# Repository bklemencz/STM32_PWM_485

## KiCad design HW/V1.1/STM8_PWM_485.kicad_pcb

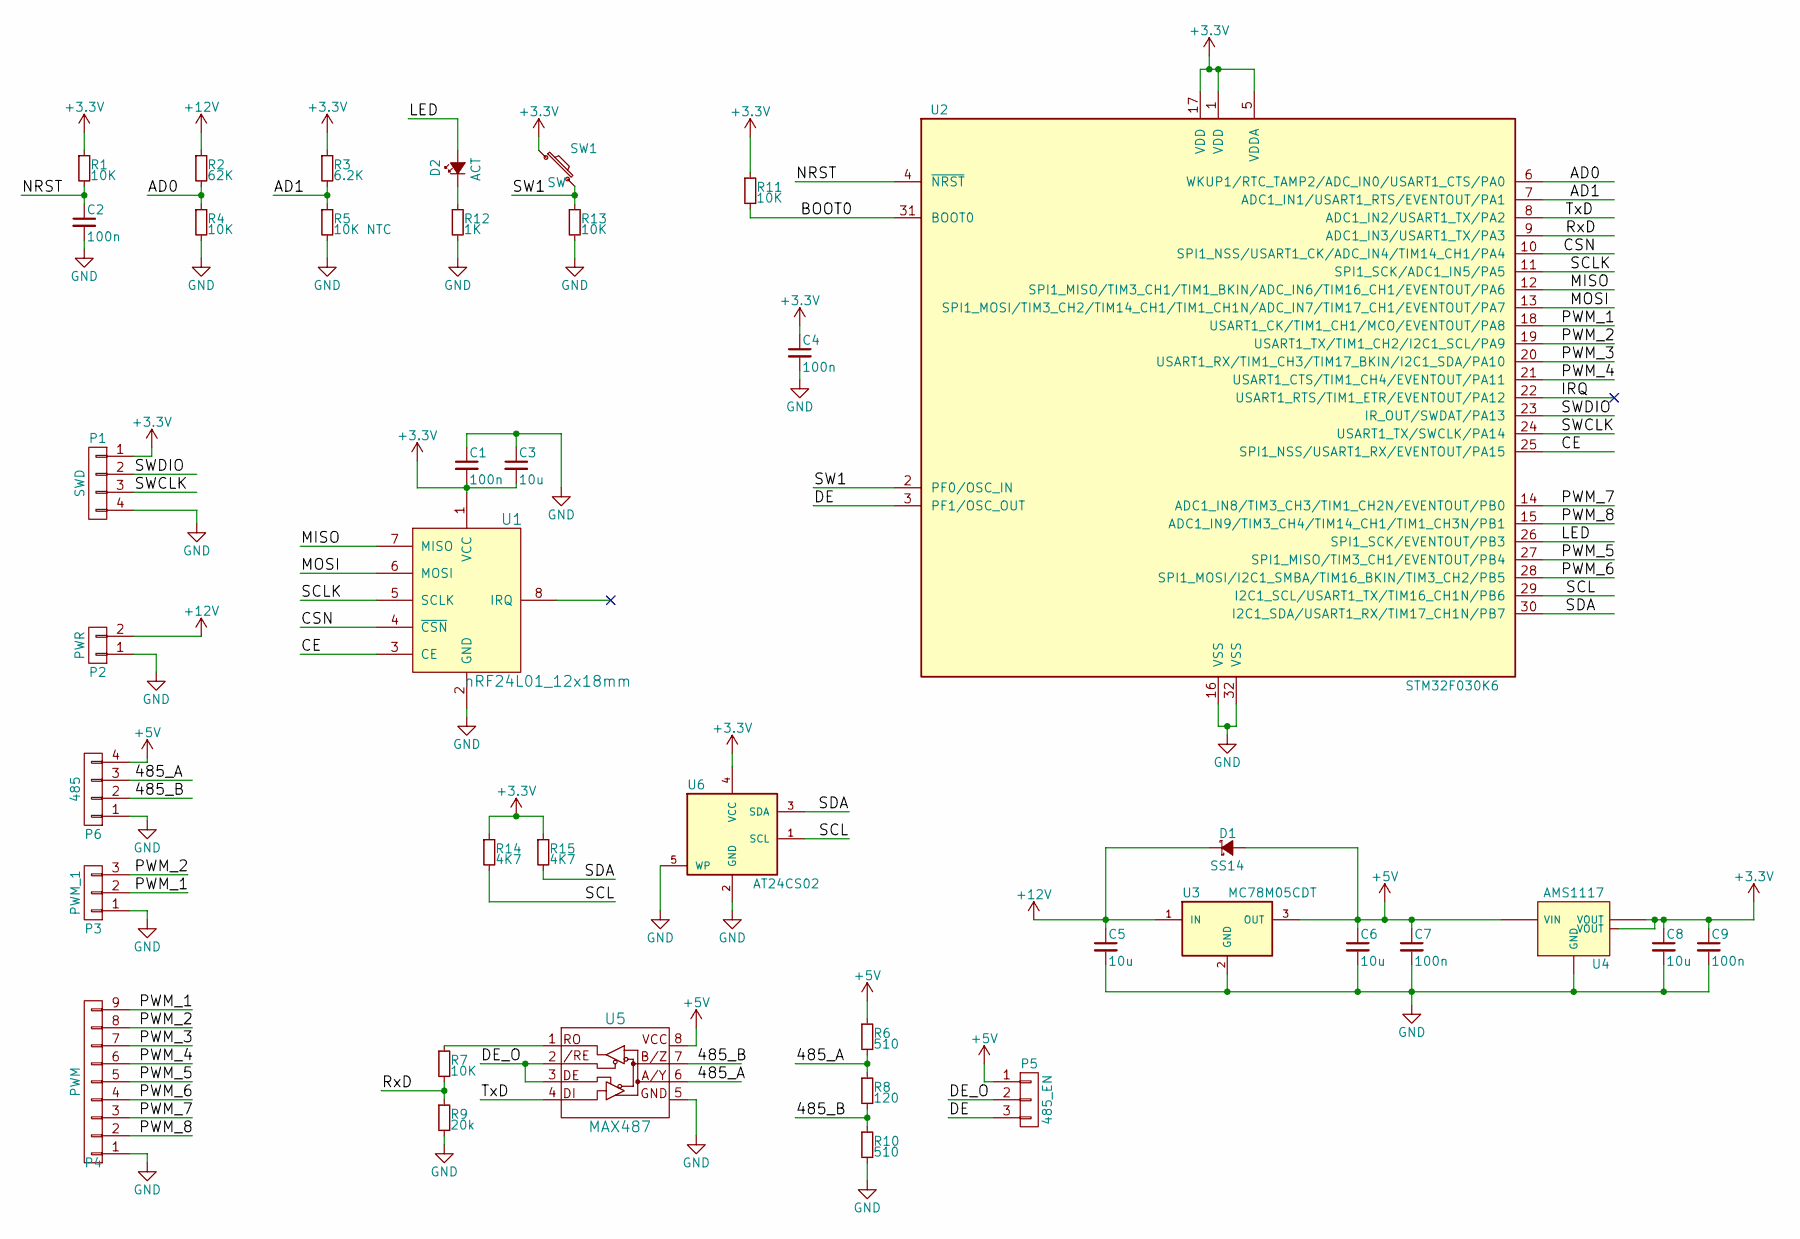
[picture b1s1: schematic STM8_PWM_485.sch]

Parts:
C1, C2, C4, C7, C9: 100n; C_0805
C3, C6, C8: 10u; C_0805
C5: 10u; C_1206
D1: SS14; D_SMA
D2: ACT; LED_0805
P1: SWD; Pin_Header_Straight_1x04_Pitch2.54mm
P2: PWR; Pin_Header_Straight_1x02_Pitch2.54mm
P3: PWM_1; Pin_Header_Straight_1x03_Pitch2.54mm
P4: PWM; Pin_Header_Straight_1x09_Pitch2.54mm
P5: 485_EN; Pin_Header_Straight_1x03_Pitch2.54mm
P6: 485; Pin_Header_Straight_1x04_Pitch2.54mm
R1, R7, R11, R13: 10K; R_0603
R2: 62K; R_0805
R3: 6.2K; R_0805
R4: 10K; R_0805
R5: 10K NTC; R_0805
R6, R10: 510; R_0603
R8: 120; R_0603
R9: 20k; R_0603
R12: 1K; R_0805
R14, R15: 4K7; R_0603
SW1: SW; Pin_Header_Straight_1x02_Pitch2.00mm
U1: nRF24L01_12x18mm; NRF24L01_12x18mm
U2: STM32F030K6; LQFP-32_7x7mm_Pitch0.8mm
U3: MC78M05CDT; TO-252-2
U4: AMS1117; SOT-223
U5: MAX487; SOIC-8_3.9x4.9mm_Pitch1.27mm
U6: AT24CS02; SOT-23-5

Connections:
+3V3: C1.2, C3.2, C4.1, C8.1, C9.1, P1.1, R1.1, R3.1, R11.1, R14.1, R15.1, SW1.1, U1.1 (VCC), U2.1 (VDD), U2.5 (VDDA), U2.17 (VDD), U4.2 (VOUT), U4.4 (VOUT), U6.4 (VCC)
+5V: C6.1, C7.1, D1.2 (A), P5.1, P6.4, R6.1, U3.3 (OUT), U4.3 (VIN), U5.8 (VCC)
+12V: C5.1, D1.1 (K), P2.2, R2.1, U3.1 (IN)
/485_A: P6.3, R6.2, R8.1, U5.6 (A/Y)
/485_B: P6.2, R8.2, R10.1, U5.7 (B/Z)
/AD0: R2.2, R4.1, U2.6 (WKUP1/RTC_TAMP2/ADC_IN0/USART1_CTS/PA0)
/AD1: R3.2, R5.1, U2.7 (ADC1_IN1/USART1_RTS/EVENTOUT/PA1)
/BOOT0: R11.2, U2.31 (BOOT0)
/CE: U1.3 (CE), U2.25 (SPI1_NSS/USART1_RX/EVENTOUT/PA15)
/CSN: U1.4 (~CSN), U2.10 (SPI1_NSS/USART1_CK/ADC_IN4/TIM14_CH1/PA4)
/DE: P5.3, U2.3 (PF1/OSC_OUT)
/DE_O: P5.2, U5.2 (/RE), U5.3 (DE)
/IRQ: U2.22 (USART1_RTS/TIM1_ETR/EVENTOUT/PA12)
/LED: D2.2 (A), U2.26 (SPI1_SCK/EVENTOUT/PB3)
/MISO: U1.7 (MISO), U2.12 (SPI1_MISO/TIM3_CH1/TIM1_BKIN/ADC_IN6/TI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)
/MOSI: U1.6 (MOSI), U2.13 (SPI1_MOSI/TIM3_CH2/TIM14_CH1/TIM1_CH1N/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)
/NRST: C2.1, R1.2, U2.4 (~NRST)
/PWM_1: P3.2, P4.9, U2.18 (USART1_CK/TIM1_CH1/MCO/EVENTOUT/PA8)
/PWM_2: P3.3, P4.8, U2.19 (USART1_TX/TIM1_CH2/I2C1_SCL/PA9)
/PWM_3: P4.7, U2.20 (USART1_RX/TIM1_CH3/TIM17_BKIN/I2C1_SDA/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)
/PWM_4: P4.6, U2.21 (USART1_CTS/TIM1_CH4/EVENTOUT/PA11)
/PWM_5: P4.5, U2.27 (SPI1_MISO/TIM3_CH1/EVENTOUT/PB4)
/PWM_6: P4.4, U2.28 (SPI1_MOSI/I2C1_SMBA/TIM16_BKIN/TIM3_CH2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)
/PWM_7: P4.3, U2.14 (ADC1_IN8/TIM3_CH3/TIM1_CH2N/EVENTOUT/PB0)
/PWM_8: P4.2, U2.15 (ADC1_IN9/TIM3_CH4/TIM14_CH1/TIM1_CH3N/P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)
/RxD: R7.2, R9.1, U2.9 (ADC1_IN3/USART1_TX/PA3)
/SCL: R14.2, U2.29 (I2C1_SCL/USART1_TX/TIM16_CH1N/PB6), U6.1 (SCL)
/SCLK: U1.5 (SCLK), U2.11 (SPI1_SCK/ADC1_IN5/PA5)
/SDA: R15.2, U2.30 (I2C1_SDA/USART1_RX/TIM17_CH1N/PB7), U6.3 (SDA)
/SW1: R13.1, SW1.2, U2.2 (PF0/OSC_IN)
/SWCLK: P1.3, U2.24 (USART1_TX/SWCLK/PA14)
/SWDIO: P1.2, U2.23 (IR_OUT/SWDAT/PA13)
/TxD: U2.8 (ADC1_IN2/USART1_TX/PA2), U5.4 (DI)
GND: C1.1, C2.2, C3.1, C4.2, C5.2, C6.2, C7.2, C8.2, C9.2, P1.4, P2.1, P3.1, P4.1, P6.1, R4.2, R5.2, R9.2, R10.2, R12.2, R13.2, U1.2 (GND), U2.16 (VSS), U2.32 (VSS), U3.2 (GND), U4.1 (GND), U5.5 (GND), U6.2 (GND), U6.5 (WP)
unnamed: D2.1 (K), R12.1
unnamed: R7.1, U5.1 (RO)

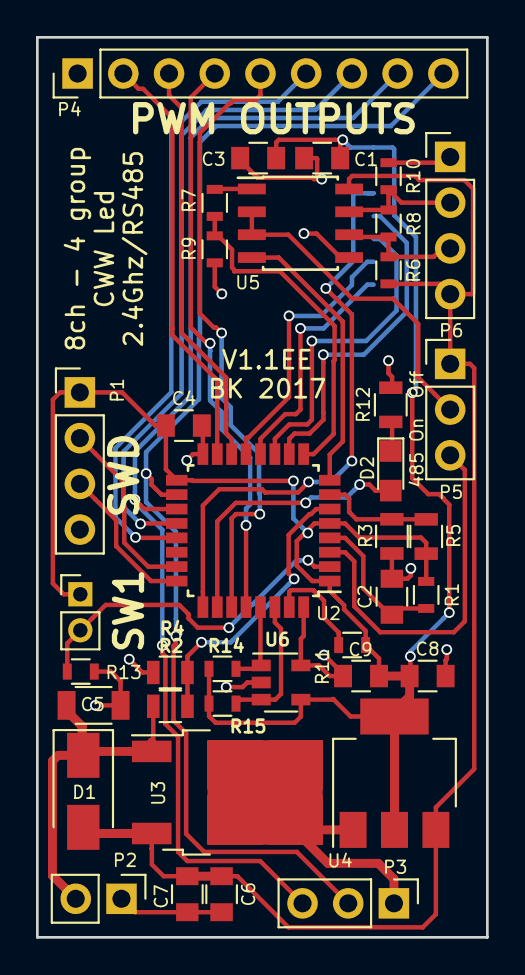
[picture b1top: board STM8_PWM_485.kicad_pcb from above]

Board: 2 copper layers, 25.0 x 50.0 mm, 39 parts (1 on the bottom side), 35 nets.

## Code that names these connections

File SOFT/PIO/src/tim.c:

/**
  ******************************************************************************
  * File Name          : TIM.c
  * Description        : This file provides code for the configuration
  *                      of the TIM instances.
  ******************************************************************************
  *
  * COPYRIGHT(c) 2017 STMicroelectronics
  *
  * Redistribution and use in source and binary forms, with or without modification,
  * are permitted provided that the following conditions are met:
  *   1. Redistributions of source code must retain the above copyright notice,
  *      this list of conditions and the following disclaimer.
  *   2. Redistributions in binary form must reproduce the above copyright notice,
  *      this list of conditions and the following disclaimer in the documentation
  *      and/or other materials provided with the distribution.
  *   3. Neither the name of STMicroelectronics nor the names of its contributors
  *      may be used to endorse or promote products derived from this software
  *      without specific prior written permission.
  *
  * THIS SOFTWARE IS PROVIDED BY THE COPYRIGHT HOLDERS AND CONTRIBUTORS "AS IS"
  * AND ANY EXPRESS OR IMPLIED WARRANTIES, INCLUDING, BUT NOT LIMITED TO, THE
  * IMPLIED WARRANTIES OF MERCHANTABILITY AND FITNESS FOR A PARTICULAR PURPOSE ARE
  * DISCLAIMED. IN NO EVENT SHALL THE COPYRIGHT HOLDER OR CONTRIBUTORS BE LIABLE
  * FOR ANY DIRECT, INDIRECT, INCIDENTAL, SPECIAL, EXEMPLARY, OR CONSEQUENTIAL
  * DAMAGES (INCLUDING, BUT NOT LIMITED TO, PROCUREMENT OF SUBSTITUTE GOODS OR
  * SERVICES; LOSS OF USE, DATA, OR PROFITS; OR BUSINESS INTERRUPTION) HOWEVER
  * CAUSED AND ON ANY THEORY OF LIABILITY, WHETHER IN CONTRACT, STRICT LIABILITY,
  * OR TORT (INCLUDING NEGLIGENCE OR OTHERWISE) ARISING IN ANY WAY OUT OF THE USE
  * OF THIS SOFTWARE, EVEN IF ADVISED OF THE POSSIBILITY OF SUCH DAMAGE.
  *
  ******************************************************************************
  */

/* Includes ------------------------------------------------------------------*/
#include "tim.h"

/* USER CODE BEGIN 0 */

/* USER CODE END 0 */

TIM_HandleTypeDef htim1;
TIM_HandleTypeDef htim3;

/* TIM1 init function */
void MX_TIM1_Init(void)
{
  TIM_MasterConfigTypeDef sMasterConfig;
  TIM_OC_InitTypeDef sConfigOC;
  TIM_BreakDeadTimeConfigTypeDef sBreakDeadTimeConfig;

  htim1.Instance = TIM1;
  htim1.Init.Prescaler = 49;
  htim1.Init.CounterMode = TIM_COUNTERMODE_UP;
  htim1.Init.Period = 1001;
  htim1.Init.ClockDivision = TIM_CLOCKDIVISION_DIV1;
  htim1.Init.RepetitionCounter = 0;
  htim1.Init.AutoReloadPreload = TIM_AUTORELOAD_PRELOAD_DISABLE;
  if (HAL_TIM_PWM_Init(&htim1) != HAL_OK)
  {
    Error_Handler();
  }

  sMasterConfig.MasterOutputTrigger = TIM_TRGO_RESET;
  sMasterConfig.MasterSlaveMode = TIM_MASTERSLAVEMODE_DISABLE;
  if (HAL_TIMEx_MasterConfigSynchronization(&htim1, &sMasterConfig) != HAL_OK)
  {
    Error_Handler();
  }

  sConfigOC.OCMode = TIM_OCMODE_PWM1;
  sConfigOC.Pulse = 0;
  sConfigOC.OCPolarity = TIM_OCPOLARITY_HIGH;
  sConfigOC.OCNPolarity = TIM_OCNPOLARITY_HIGH;
  sConfigOC.OCFastMode = TIM_OCFAST_DISABLE;
  sConfigOC.OCIdleState = TIM_OCIDLESTATE_RESET;
  sConfigOC.OCNIdleState = TIM_OCNIDLESTATE_RESET;
  if (HAL_TIM_PWM_ConfigChannel(&htim1, &sConfigOC, TIM_CHANNEL_1) != HAL_OK)
  {
    Error_Handler();
  }

  if (HAL_TIM_PWM_ConfigChannel(&htim1, &sConfigOC, TIM_CHANNEL_2) != HAL_OK)
  {
    Error_Handler();
  }

  if (HAL_TIM_PWM_ConfigChannel(&htim1, &sConfigOC, TIM_CHANNEL_3) != HAL_OK)
  {
    Error_Handler();
  }

  if (HAL_TIM_PWM_ConfigChannel(&htim1, &sConfigOC, TIM_CHANNEL_4) != HAL_OK)
  {
    Error_Handler();
  }

  sBreakDeadTimeConfig.OffStateRunMode = TIM_OSSR_DISABLE;
  sBreakDeadTimeConfig.OffStateIDLEMode = TIM_OSSI_DISABLE;
  sBreakDeadTimeConfig.LockLevel = TIM_LOCKLEVEL_OFF;
  sBreakDeadTimeConfig.DeadTime = 0;
  sBreakDeadTimeConfig.BreakState = TIM_BREAK_DISABLE;
  sBreakDeadTimeConfig.BreakPolarity = TIM_BREAKPOLARITY_HIGH;
  sBreakDeadTimeConfig.AutomaticOutput = TIM_AUTOMATICOUTPUT_DISABLE;
  if (HAL_TIMEx_ConfigBreakDeadTime(&htim1, &sBreakDeadTimeConfig) != HAL_OK)
  {
    Error_Handler();
  }

  HAL_TIM_MspPostInit(&htim1);

}
/* TIM3 init function */
void MX_TIM3_Init(void)
{
  TIM_MasterConfigTypeDef sMasterConfig;
  TIM_OC_InitTypeDef sConfigOC;

  htim3.Instance = TIM3;
  htim3.Init.Prescaler = 49;
  htim3.Init.CounterMode = TIM_COUNTERMODE_UP;
  htim3.Init.Period = 1001;
  htim3.Init.ClockDivision = TIM_CLOCKDIVISION_DIV1;
  htim3.Init.AutoReloadPreload = TIM_AUTORELOAD_PRELOAD_DISABLE;
  if (HAL_TIM_PWM_Init(&htim3) != HAL_OK)
  {
    Error_Handler();
  }

  sMasterConfig.MasterOutputTrigger = TIM_TRGO_RESET;
  sMasterConfig.MasterSlaveMode = TIM_MASTERSLAVEMODE_DISABLE;
  if (HAL_TIMEx_MasterConfigSynchronization(&htim3, &sMasterConfig) != HAL_OK)
  {
    Error_Handler();
  }

  sConfigOC.OCMode = TIM_OCMODE_PWM1;
  sConfigOC.Pulse = 0;
  sConfigOC.OCPolarity = TIM_OCPOLARITY_HIGH;
  sConfigOC.OCFastMode = TIM_OCFAST_DISABLE;
  if (HAL_TIM_PWM_ConfigChannel(&htim3, &sConfigOC, TIM_CHANNEL_1) != HAL_OK)
  {
    Error_Handler();
  }

  if (HAL_TIM_PWM_ConfigChannel(&htim3, &sConfigOC, TIM_CHANNEL_2) != HAL_OK)
  {
    Error_Handler();
  }

  if (HAL_TIM_PWM_ConfigChannel(&htim3, &sConfigOC, TIM_CHANNEL_3) != HAL_OK)
  {
    Error_Handler();
  }

  if (HAL_TIM_PWM_ConfigChannel(&htim3, &sConfigOC, TIM_CHANNEL_4) != HAL_OK)
  {
    Error_Handler();
  }

  HAL_TIM_MspPostInit(&htim3);

}

void HAL_TIM_PWM_MspInit(TIM_HandleTypeDef* tim_pwmHandle)
{

  if(tim_pwmHandle->Instance==TIM1)
  {
  /* USER CODE BEGIN TIM1_MspInit 0 */

  /* USER CODE END TIM1_MspInit 0 */
    /* Peripheral clock enable */
    __HAL_RCC_TIM1_CLK_ENABLE();
  /* USER CODE BEGIN TIM1_MspInit 1 */

  /* USER CODE END TIM1_MspInit 1 */
  }
  else if(tim_pwmHandle->Instance==TIM3)
  {
  /* USER CODE BEGIN TIM3_MspInit 0 */

  /* USER CODE END TIM3_MspInit 0 */
    /* Peripheral clock enable */
    __HAL_RCC_TIM3_CLK_ENABLE();
  /* USER CODE BEGIN TIM3_MspInit 1 */

  /* USER CODE END TIM3_MspInit 1 */
  }
}
void HAL_TIM_MspPostInit(TIM_HandleTypeDef* timHandle)
{

  GPIO_InitTypeDef GPIO_InitStruct;
  if(timHandle->Instance==TIM1)
  {
  /* USER CODE BEGIN TIM1_MspPostInit 0 */

  /* USER CODE END TIM1_MspPostInit 0 */
    /**TIM1 GPIO Configuration
    PA8     ------> TIM1_CH1
    PA9     ------> TIM1_CH2
    PA10     ------> TIM1_CH3
    PA11     ------> TIM1_CH4
    */
    GPIO_InitStruct.Pin = GPIO_PIN_8|GPIO_PIN_9|GPIO_PIN_10|GPIO_PIN_11;
    GPIO_InitStruct.Mode = GPIO_MODE_AF_PP;
    GPIO_InitStruct.Pull = GPIO_NOPULL;
    GPIO_InitStruct.Speed = GPIO_SPEED_FREQ_HIGH;
    GPIO_InitStruct.Alternate = GPIO_AF2_TIM1;
    HAL_GPIO_Init(GPIOA, &GPIO_InitStruct);

    GPIO_InitStruct.Pin = GPIO_PIN_8|GPIO_PIN_9|GPIO_PIN_10|GPIO_PIN_11;
    GPIO_InitStruct.Mode = GPIO_MODE_AF_PP;
    GPIO_InitStruct.Pull = GPIO_NOPULL;
    GPIO_InitStruct.Speed = GPIO_SPEED_FREQ_HIGH;
    HAL_GPIO_Init(GPIOA, &GPIO_InitStruct);

    HAL_I2CEx_EnableFastModePlus(SYSCFG_CFGR1_I2C_FMP_PA9);

    HAL_I2CEx_EnableFastModePlus(SYSCFG_CFGR1_I2C_FMP_PA10);

  /* USER CODE BEGIN TIM1_MspPostInit 1 */

  /* USER CODE END TIM1_MspPostInit 1 */
  }
  else if(timHandle->Instance==TIM3)
  {
  /* USER CODE BEGIN TIM3_MspPostInit 0 */

  /* USER CODE END TIM3_MspPostInit 0 */

    /**TIM3 GPIO Configuration
    PB0     ------> TIM3_CH3
    PB1     ------> TIM3_CH4
    PB4     ------> TIM3_CH1
    PB5     ------> TIM3_CH2
    */
    GPIO_InitStruct.Pin = GPIO_PIN_0|GPIO_PIN_1|GPIO_PIN_4|GPIO_PIN_5;
    GPIO_InitStruct.Mode = GPIO_MODE_AF_PP;
    GPIO_InitStruct.Pull = GPIO_NOPULL;
    GPIO_InitStruct.Speed = GPIO_SPEED_FREQ_HIGH;
    GPIO_InitStruct.Alternate = GPIO_AF1_TIM3;
    HAL_GPIO_Init(GPIOB, &GPIO_InitStruct);

    GPIO_InitStruct.Pin = GPIO_PIN_0|GPIO_PIN_1|GPIO_PIN_4|GPIO_PIN_5;
    GPIO_InitStruct.Mode = GPIO_MODE_AF_PP;
    GPIO_InitStruct.Pull = GPIO_NOPULL;
    GPIO_InitStruct.Speed = GPIO_SPEED_FREQ_HIGH;
    HAL_GPIO_Init(GPIOB, &GPIO_InitStruct);

  /* USER CODE BEGIN TIM3_MspPostInit 1 */

  /* USER CODE END TIM3_MspPostInit 1 */
  }

}

void HAL_TIM_PWM_MspDeInit(TIM_HandleTypeDef* tim_pwmHandle)
{

  if(tim_pwmHandle->Instance==TIM1)
  {
  /* USER CODE BEGIN TIM1_MspDeInit 0 */

  /* USER CODE END TIM1_MspDeInit 0 */
    /* Peripheral clock disable */
    __HAL_RCC_TIM1_CLK_DISABLE();
  /* USER CODE BEGIN TIM1_MspDeInit 1 */

  /* USER CODE END TIM1_MspDeInit 1 */
  }
  else if(tim_pwmHandle->Instance==TIM3)
  {
  /* USER CODE BEGIN TIM3_MspDeInit 0 */

  /* USER CODE END TIM3_MspDeInit 0 */
    /* Peripheral clock disable */
    __HAL_RCC_TIM3_CLK_DISABLE();
  /* USER CODE BEGIN TIM3_MspDeInit 1 */

  /* USER CODE END TIM3_MspDeInit 1 */
  }
}

/* USER CODE BEGIN 1 */

/* USER CODE END 1 */

/**
  * @}
  */

/**
  * @}
  */

/************************ (C) COPYRIGHT STMicroelectronics *****END OF FILE****/

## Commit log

2017-06-26 :tada: Added .gitattributes & .gitignore files
2017-06-26 Initial
2017-06-27 hange to STM32
2017-06-27 PCB UPdate
2017-09-07 PIO Create
